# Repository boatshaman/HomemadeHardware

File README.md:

# Homemade Hardware
### Projects from homemade hardware ITP course with Andrew Sigler 
##### Joseph Hensersky | JH5363

* [ATtiny85 Programming Rig in class exercise](https://github.com/boatshaman/HomemadeHardware/tree/master/ATtiny85_Jig)
* [ATtiny85 First Interaction](https://github.com/boatshaman/HomemadeHardware/tree/master/firstInteraction_ATtiny85)
* [Lipo Battery Charger Circuit Board in class exercise](https://github.com/boatshaman/HomemadeHardware/tree/master/lipo_batt_charger)
* [Eagle First Homework](https://github.com/boatshaman/HomemadeHardware/tree/master/EagleFirstHW)
* [Marquee Board - Letter 'O'](https://github.com/boatshaman/HomemadeHardware/tree/master/Marquee)
* [Final Project BOM](https://github.com/boatshaman/HomemadeHardware/blob/master/FinalProject_BOM)
* [Final Project](https://github.com/boatshaman/HomemadeHardware/tree/master/Final%20Board)

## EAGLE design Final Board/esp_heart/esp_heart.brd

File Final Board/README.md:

# Final Board - Capacitive Touch Heart

Okay so my final board ended up being a heart shaped board that has LEDs in the front in the shape of a heart along with a capacitive touch pad in the front. The LEDs are turned on when the capactive touch pad is pressed. I used a SMD ATtiny85 as the microcontroller and had wires soldered to the programming pins originally and just desoldered them after it had been programmed correctly. Here are pictures of the board along with the board design: 

Board and Schematic files can be found [here](https://github.com/boatshaman/HomemadeHardware/tree/master/Final%20Board/finschem) and the parts list has been updated in my [Final Project BOM](https://github.com/boatshaman/HomemadeHardware/tree/master/FinalProject_BOM). 

I think the coolest part about this board is that all the copper pours on the front are actually connected to the microcontroller. The outermost heart is the LED ground connected to the transistor, middle heart is vcc, innermost heart is the capacitive touch pad. Figuring out how to do the DXF files, polygon stuff, and connecting them to specific nets was a bit of a struggle but afterwards I got really quite good at using these features in EAGLE.

[Here](https://www.youtube.com/watch?v=mon0F_LehNs) is a video of the interaction 

I wanted to connect this board to a project I was creating for another class that would have it connected to the Adafruit IO MQTT broker. Originally I was planning on connecting some of the wires from the board to an ESP8266 Feather Huzzah I had but then realized that I could just put the ESP8266 on the heart itself! The generic ESP8266 is small enough and then I wouldn't be restricted to having the board connected to the microcontroller through wires. I redesigned the board with the ESP8266 as the controller. Here is the picture of the new board design:

There are two major changes in this. First is the ESP8266 of course. The ESP8266 is interesting because there are a couple pins that need to be correctly wired up for programming. DIO0 and DIO15 need to be pulled to ground and DIO2 to VCC. DIO0 usually needs to not be connected to ground though so I had add a button which I would press during programming. Another thing I needed for programming but didn't realize until after I had the board printed was I needed a connection from reset to the FTDI USB to serial programmer. It was really nerve wracking when I first tried to program the board after assembling it all and the code just wouldn't upload. I got around this but physically holding a wire to this pin during programming. 

I also forgot to connect one of the nets :'( 
I got around this buy soldering a wire to complete the connection. 

The final change that was neccessary was adding a regulator because the ESP8266 module excepts a maximum input voltage of 3.6 volts and even the lipo batteries give off a higher voltage when fully charged. As I wasn't able to order parts for this I just looked around the hard lab to find a regulator and settled on the UA78M33CDCYR 3.3v regulator. This was a mistake. While this regulator does give off 3.3v, it needs above a 5 volt input voltage which my lipo batteries wouldn't be able to provide. I realized this when I connected my lipo battery to the completed board and I measured the voltage coming out of the regulator to be about .3 volts. I was able to get around this by attaching a 9v battery to the board. I made a 9v battery connector by ripping apart an old 9v battery and soldering to the connectors of it. 

After that I just uploaded code and removed the programming wires and it was good to go! I needed rubber bands around the heart to secure the battery though.

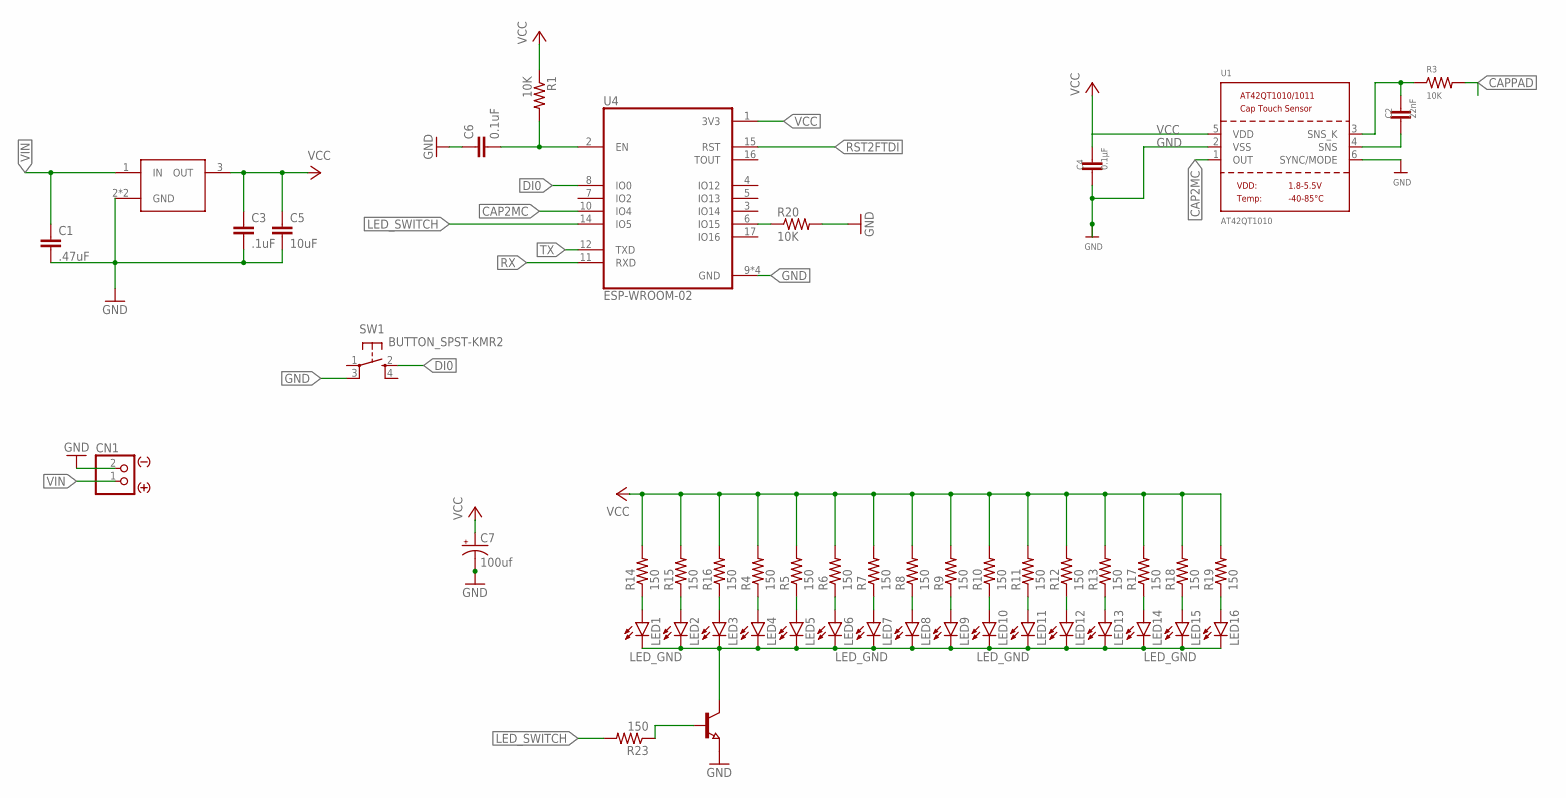
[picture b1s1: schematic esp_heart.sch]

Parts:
C1: .47uF; 0805
C2: 22nF; 0805
C3: .1uF; 0805
C4: 0.1µF; 0805
C5: 10uF; 0805
C6: 0.1uF; 0805
C7: 100uf; PANASONIC_D
CN1: JST_2PIN_BATTERY-SMT-HORIZ; JST-PH-2-SMT-RA
LED1, LED2, LED3, LED4, LED5, LED6, LED7, LED8, LED9, LED10, LED11, LED12, LED13, LED14, LED15, LED16: LED0603; LED-0603
Q5: TRANSISTOR-NPN-SOT23; SOT23
R1, R3, R20: 10K; 0805
R4, R5, R6, R7, R8, R9, R10, R11, R12, R13, R14, R15, R16, R17, R18, R19: 150; 0603-RES
R23: 150; 0805
SW1: BUTTON_SPST-KMR2; KMR2
U1: AT42QT1010; SOT23-6
U4: ESP-WROOM-02; MODULE_ESP-WROOM-02
U$1: REGULATOR3.3V-0.5A-UA78M33CDCYR; SOT223

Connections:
CAP2MC: U1.1 (OUT), U4.10 (IO4)
CAPPAD: R3.2
DI0: SW1.2 (S), U4.8 (IO0)
GND: C1.2, C3.2, C4.2, C5.2, C6.1, C7.-, CN1.2 (1), Q5.2 (E), R20.2, SW1.3 (P1), U1.2 (VSS), U1.6 (SYNC/MODE), U4.9 (GND), U4.13 (GND), U4.18 (GND), U4.19 (GND), U$1.2 (GND), U$1.4 (GND)
LED_GND: LED1.C, LED2.C, LED3.C, LED4.C, LED5.C, LED6.C, LED7.C, LED8.C, LED9.C, LED10.C, LED11.C, LED12.C, LED13.C, LED14.C, LED15.C, LED16.C, Q5.3 (C)
LED_SWITCH: R23.2, U4.14 (IO5)
unnamed: LED4.A, R4.1
unnamed: C6.2, R1.2, U4.2 (EN)
unnamed: LED15.A, R18.1
unnamed: LED1.A, R14.1
unnamed: LED2.A, R15.1
unnamed: LED5.A, R5.1
unnamed: LED6.A, R6.1
unnamed: LED7.A, R7.1
unnamed: LED8.A, R8.1
unnamed: LED9.A, R9.1
unnamed: LED10.A, R10.1
unnamed: LED11.A, R11.1
unnamed: LED12.A, R12.1
unnamed: LED13.A, R13.1
unnamed: LED3.A, R16.1
unnamed: R20.1, U4.6 (IO15)
unnamed: LED16.A, R19.1
unnamed: LED14.A, R17.1
unnamed: Q5.1 (B), R23.1
unnamed: C2.2, U1.4 (SNS)
unnamed: C2.1, R3.1, U1.3 (SNS_K)
RST2FTDI: U4.15 (RST)
RX: U4.11 (RXD)
TX: U4.12 (TXD)
VCC: C3.1, C4.1, C5.1, C7.+, R1.1, R4.2, R5.2, R6.2, R7.2, R8.2, R9.2, R10.2, R11.2, R12.2, R13.2, R14.2, R15.2, R16.2, R17.2, R18.2, R19.2, U1.5 (VDD), U4.1 (3V3), U$1.3 (OUT)
VIN: C1.1, CN1.1 (2), U$1.1 (IN)

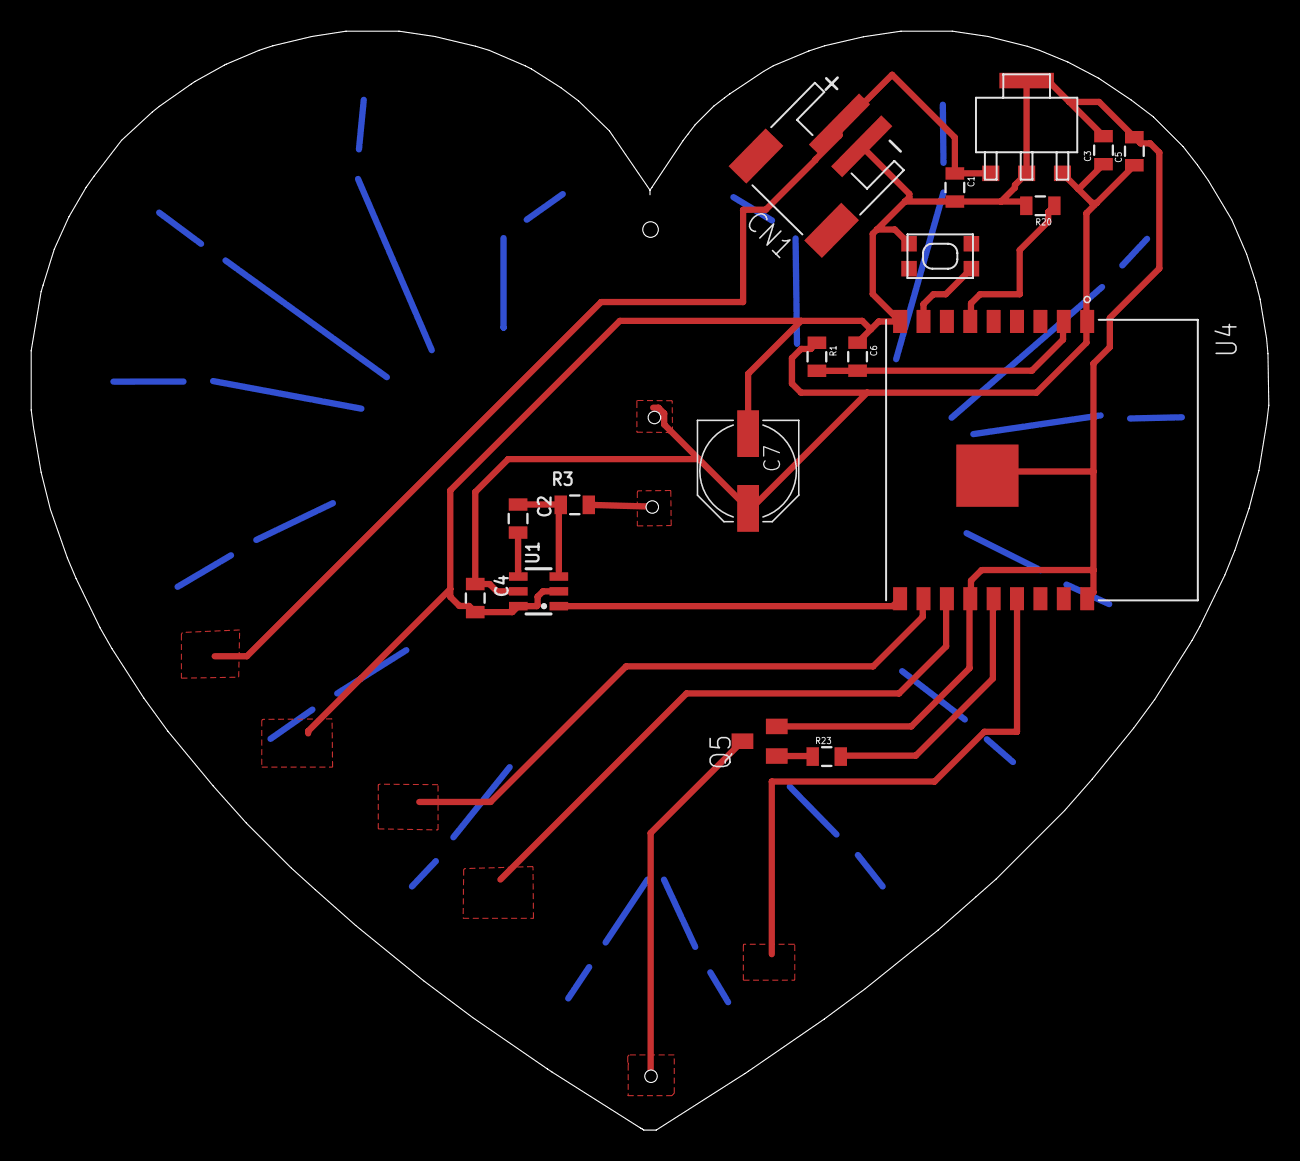
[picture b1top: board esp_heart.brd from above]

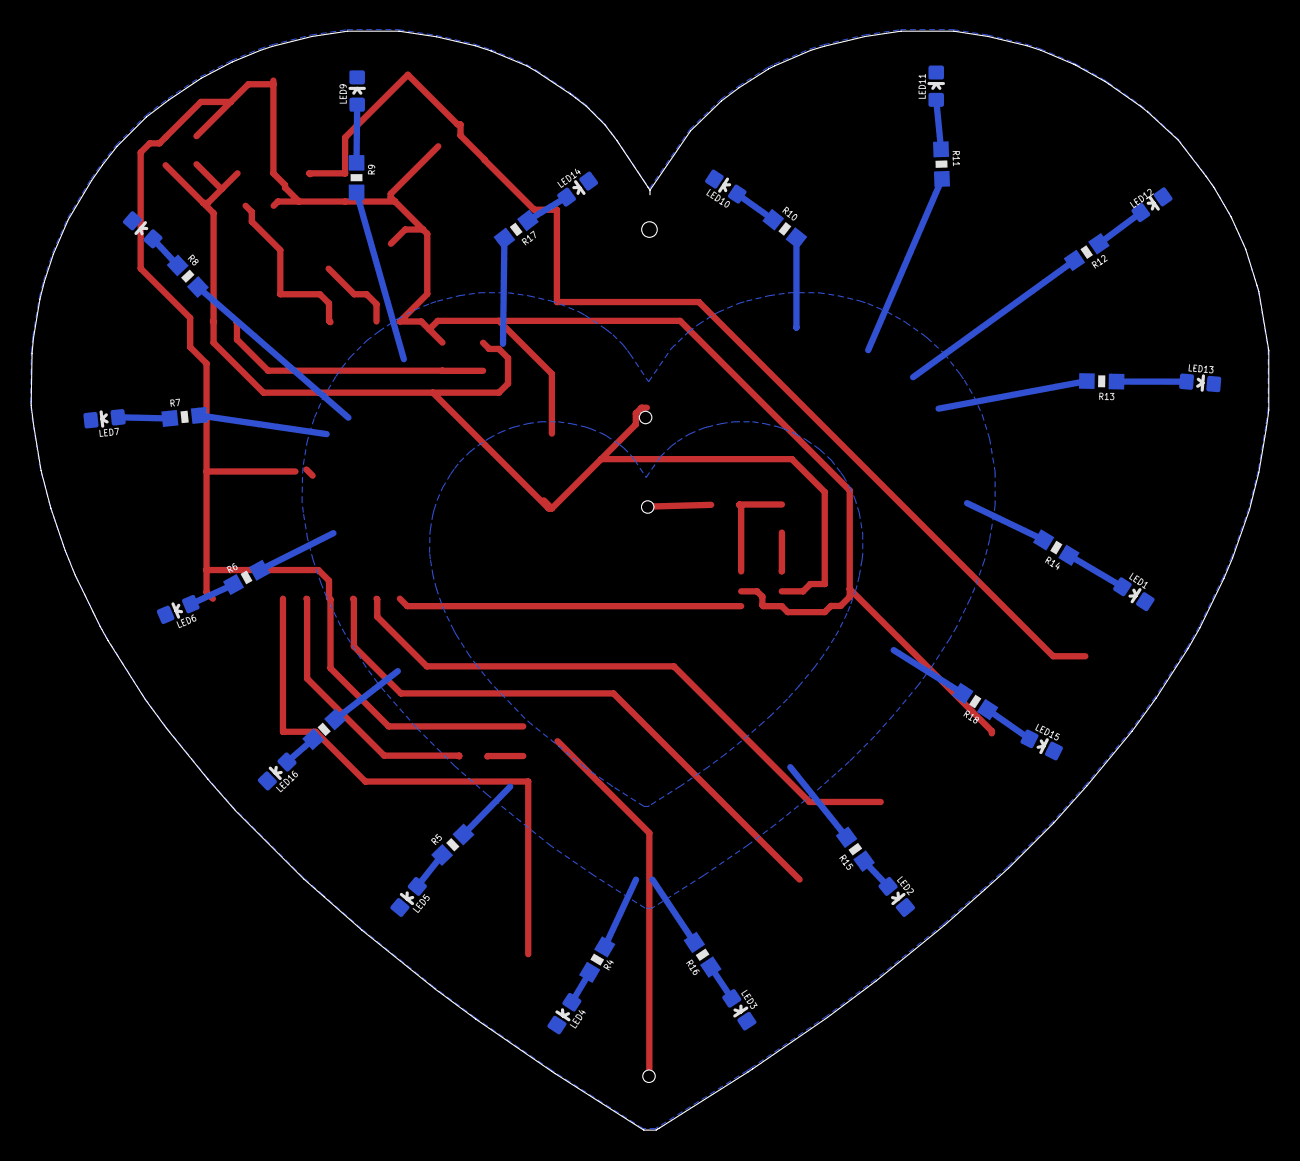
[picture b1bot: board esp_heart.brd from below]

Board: 2 copper layers, 79.4 x 70.5 mm, 49 parts (32 on the bottom side), 28 nets.

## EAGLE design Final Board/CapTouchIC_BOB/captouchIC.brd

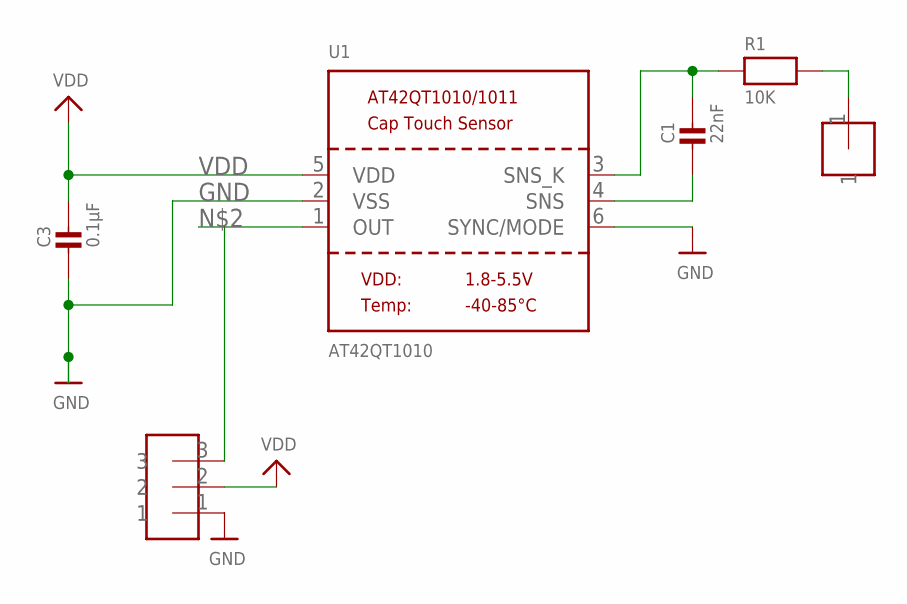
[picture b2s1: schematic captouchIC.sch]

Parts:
C1: 22nF; _0805
C3: 0.1µF; _0805
R1: 10K; _0805
U1: AT42QT1010; SOT23-6
U$1: HEADER-1-TESTPOINT; TESTPOINT-1
U$6: HEADER-3

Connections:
CAPPAD: R1.2, U$1.1
GND: C3.2, U1.2 (VSS), U1.6 (SYNC/MODE), U$6.1
unnamed: U1.1 (OUT), U$6.3
unnamed: C1.2, U1.4 (SNS)
unnamed: C1.1, R1.1, U1.3 (SNS_K)
VDD: C3.1, U1.5 (VDD), U$6.2

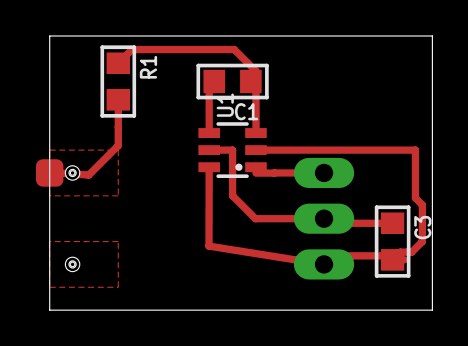
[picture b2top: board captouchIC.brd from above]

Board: 2 copper layers, 21.3 x 15.2 mm, 6 parts (0 on the bottom side), 6 nets.

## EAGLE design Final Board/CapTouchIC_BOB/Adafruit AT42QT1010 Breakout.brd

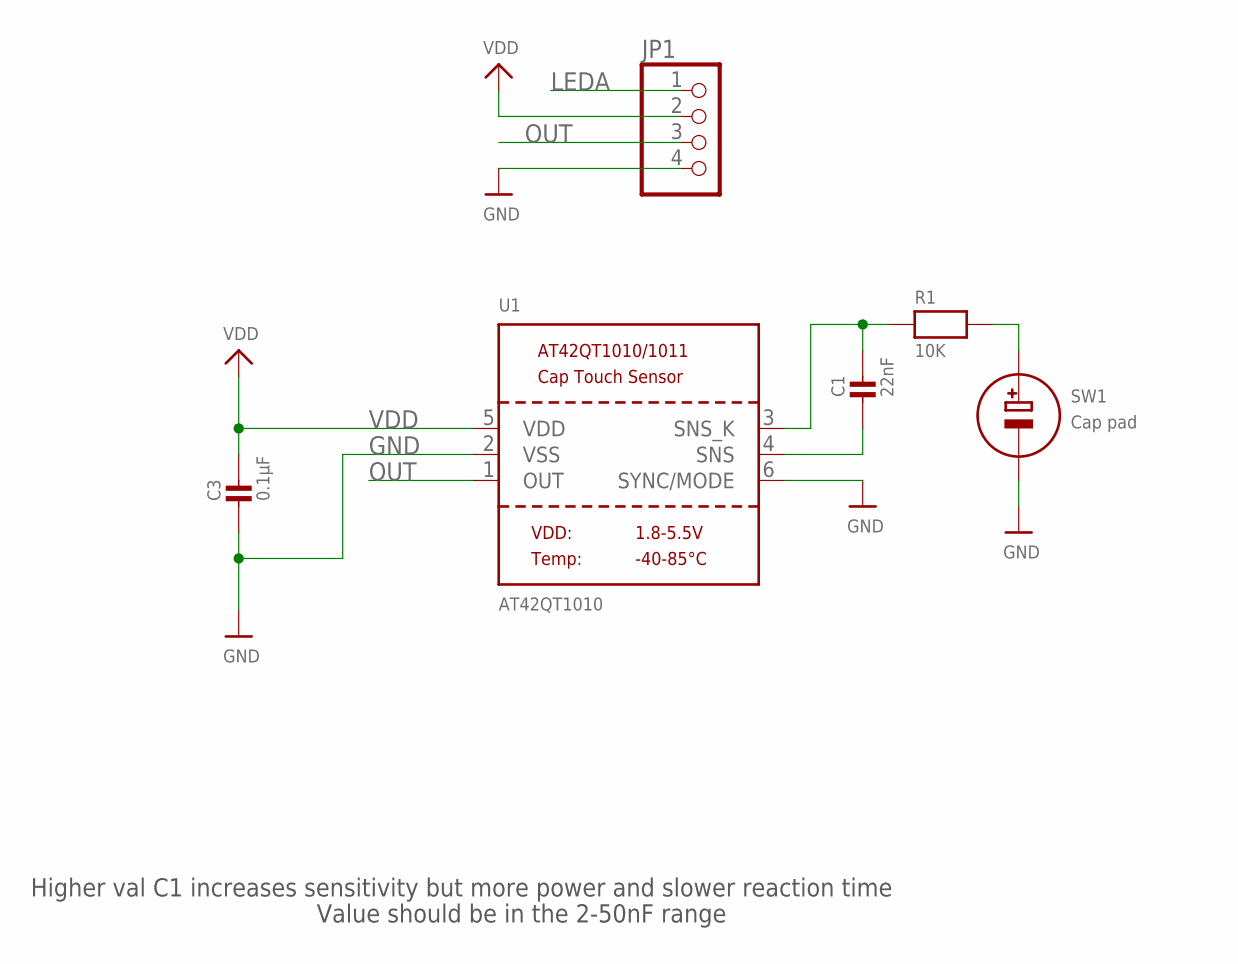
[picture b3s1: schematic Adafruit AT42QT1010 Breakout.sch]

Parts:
C1: 22nF; _0805
C3: 0.1µF; _0805
JP1: HEADER-1X476MIL; 1X04_ROUND_76
R1: 10K; _0805
SW1: Cap pad; CAPTOUCH_SIMPLE_12.5MM
U1: AT42QT1010; SOT23-6

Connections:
CAPPAD: R1.2, SW1.E (+)
GND: C3.2, JP1.4, SW1.G (-), U1.2 (VSS), U1.6 (SYNC/MODE)
LEDA: JP1.1
unnamed: C1.2, U1.4 (SNS)
unnamed: C1.1, R1.1, U1.3 (SNS_K)
OUT: JP1.3, U1.1 (OUT)
VDD: C3.1, JP1.2, U1.5 (VDD)

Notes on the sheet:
Higher val C1 increases sensitivity but more power and slower reaction time
Value should be in the 2-50nF range

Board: 2 copper layers, 6 parts (0 on the bottom side), 6 nets, no tracks yet.

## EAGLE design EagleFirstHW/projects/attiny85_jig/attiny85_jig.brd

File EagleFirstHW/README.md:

# Eagle Routing 

This homework is our first experience using the EAGLE software for the creation of PCB routing designs. 

We start with three different schematics and from that create .brd files which can be given to PCB mills in order to etch the routes onto a PCB board. While we haven't quite learned how to do that yet, this is the preliminary step and I am sure we will learn how to do this soon. 

#### ATTiny85 Programming Jig 

The first schematic we got was of the ATTiny85 Programming Jig just as we had created for our first week in-class exercise.

Here is the schematic file:

And here is my implementation of the routes for this schemeatic:

#### ATTiny85 LED 

The second schematic we got was of an ATTiny85 and LED setup. It seems this is just a very simple setup for controlling an LED with the ATTiny85

Here is the schematic file:

And here is my implementation of the routes for this schemeatic:

#### ATTiny85 Transistor 

The last schematic we got was of an ATTiny85 connected to a potentiometer and transistor. It seems to be a way for activating a larger power supply via the transistor to another electronic component. I am a little confused why a potentiometer is being used considering that is an analog switch and a transitor can only be off or on, but the professor said we will end up building this circuit board so I am sure we will find out. This one was defenitely the most difficult to figure out and I ended up needing to add a Via in order to finish the last connection. It is only one Via so it shouldn't be too difficult during the fabrication process and it gives me a chance to see what it takes to create a Via on a PCB board. 

Here is the schematic file:

And here is my implementation of the routes for this schemeatic:

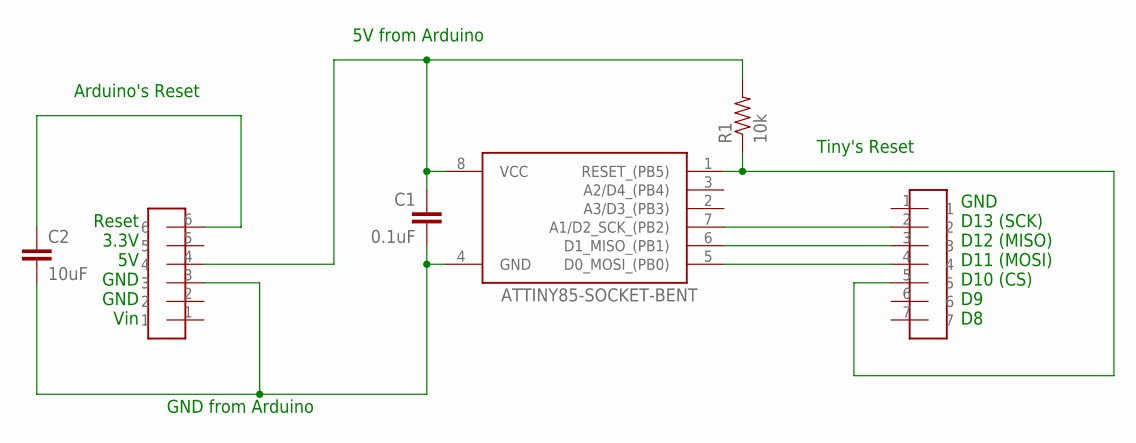
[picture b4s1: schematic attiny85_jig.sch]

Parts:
C1: 0.1uF; 0805
C2: 10uF; 0805
R1: 10k; 0805
U$1: ATTINY85-SOCKET-BENT; SOCKET-8PIN-BENT
U$2: HEADER-6
U$3: HEADER-7

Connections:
5V: C1.1, R1.2, U$1.8 (VCC), U$2.4
ARDUINO_RESET: C2.1, U$2.6
GND: C1.2, C2.2, U$1.4 (GND), U$2.3
MISO: U$1.6 (D1_MISO_(PB1)), U$3.3
MOSI: U$1.5 (D0_MOSI_(PB0)), U$3.4
SCK: U$1.7 (A1/D2_SCK_(PB2)), U$3.2
TINY_RESET: R1.1, U$1.1 (RESET_(PB5)), U$3.5

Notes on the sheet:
Arduino's Reset
GND D13 (SCK) D12 (MISO) D11 (MOSI) D10 (CS) D9 D8
Reset 3.3V 5V GND GND Vin
5V from Arduino
GND from Arduino
Tiny's Reset

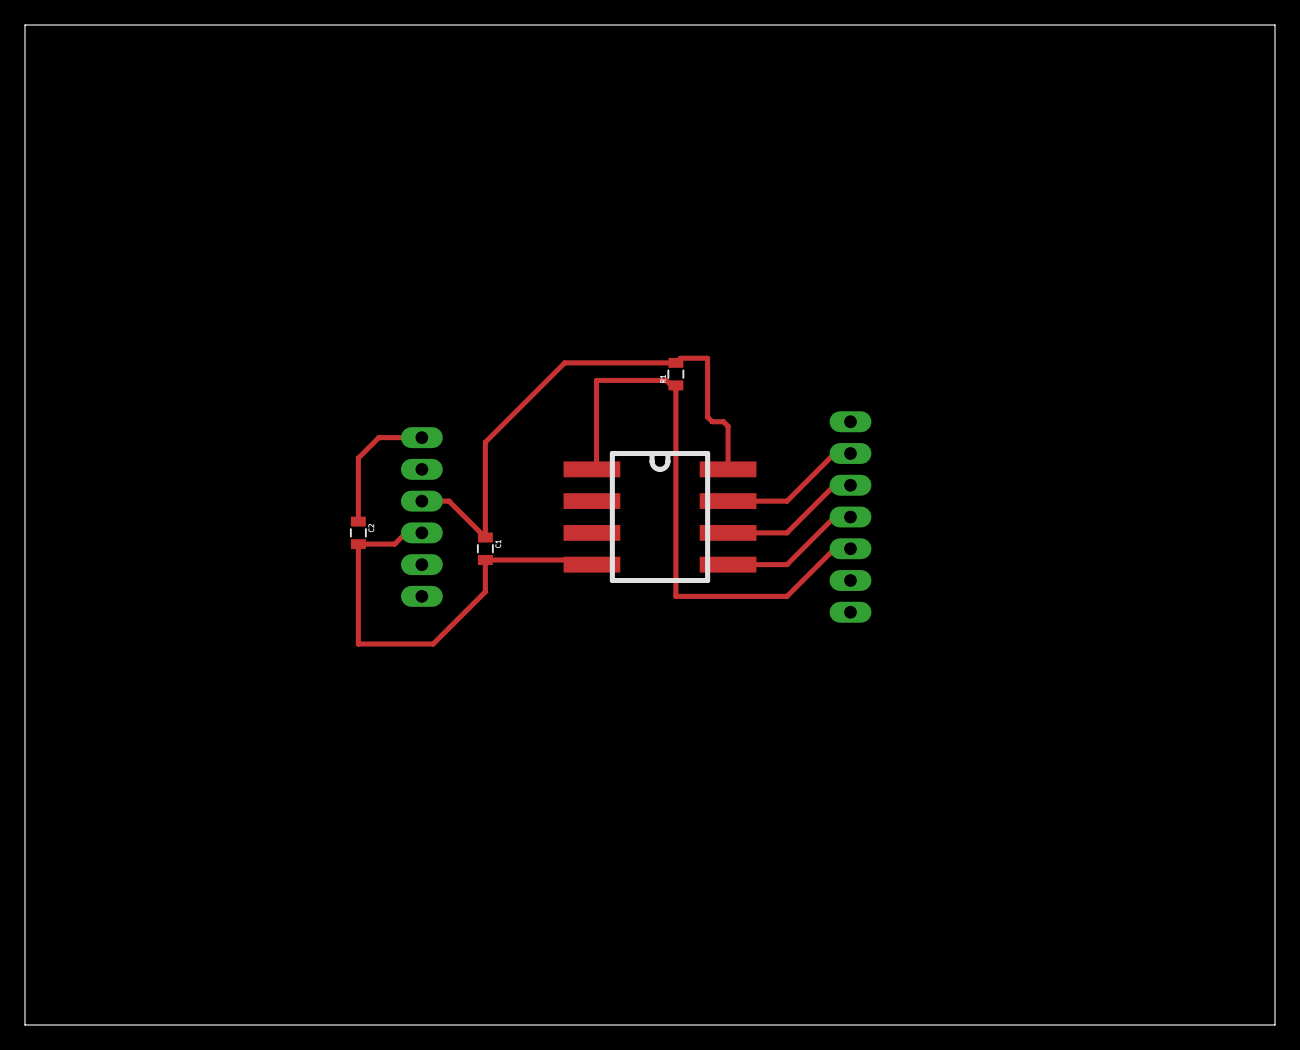
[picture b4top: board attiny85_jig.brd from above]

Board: 2 copper layers, 100.0 x 80.0 mm, 6 parts (0 on the bottom side), 7 nets.

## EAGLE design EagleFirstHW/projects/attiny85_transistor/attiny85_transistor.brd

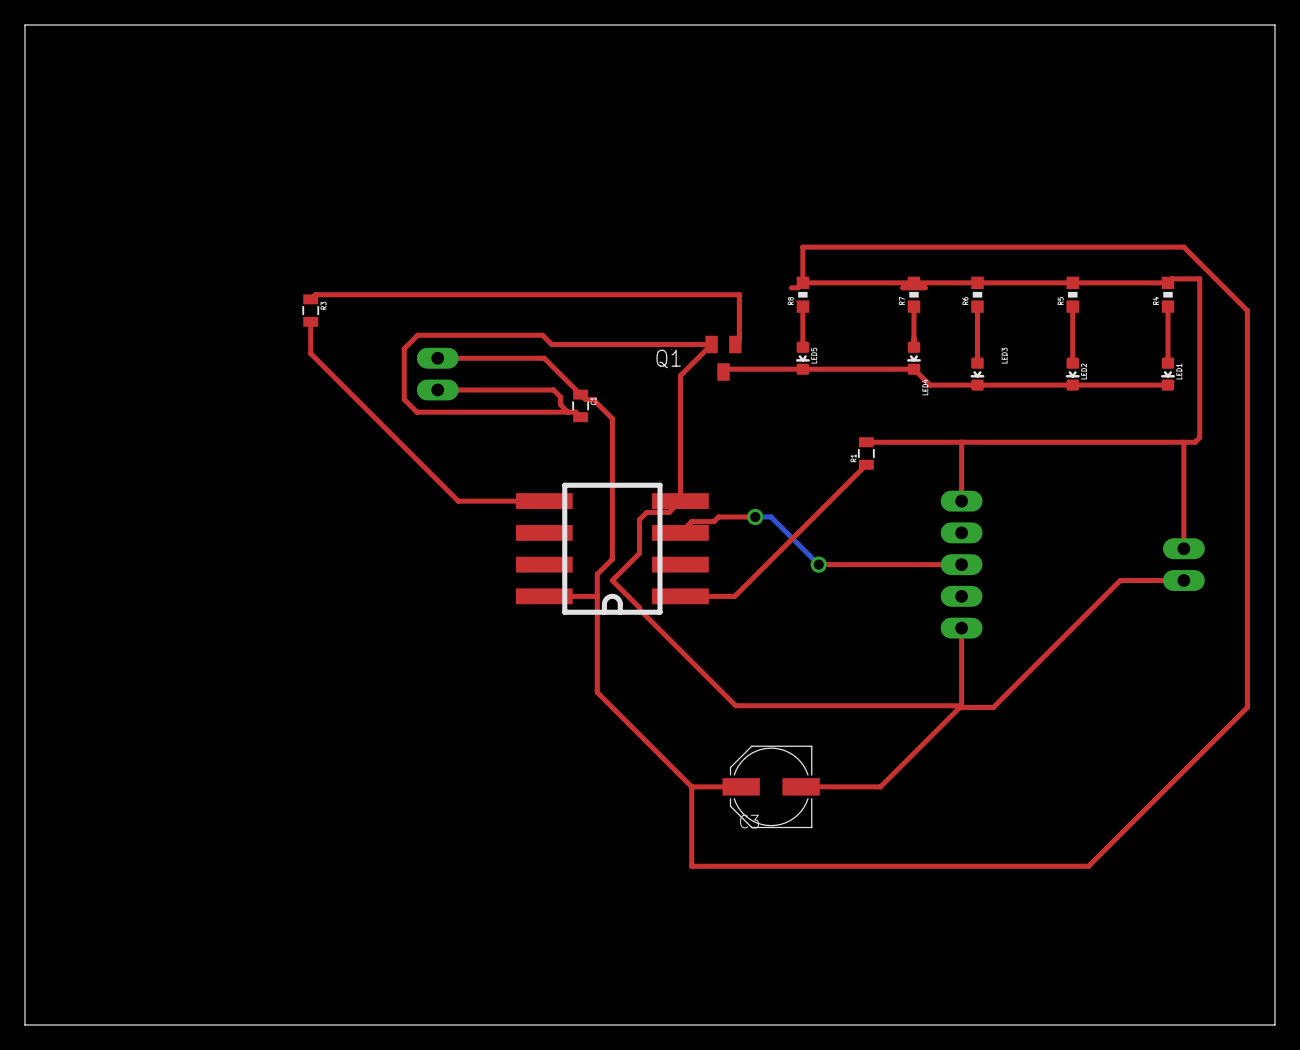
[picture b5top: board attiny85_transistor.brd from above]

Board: 2 copper layers, 100.0 x 80.0 mm, 19 parts (0 on the bottom side), 12 nets.

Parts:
C1: 0.1uF; 0805
C3: 100uF; PANASONIC_D
LED1, LED2, LED3, LED4, LED5: LED-0603
POTENTIOMETER: HEADER-5
Q1: BSH103; SOT23
R1: 10k; 0805
R3: 150; 0805
R4, R5, R6, R7, R8: 0603-RES
U$1: ATTINY85-SOCKET-BENT; SOCKET-8PIN-BENT
U$2, U$3: HEADER-2

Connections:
5V: C1.1, C3.+, POTENTIOMETER.1, R1.2, R4.2, R5.2, R6.2, R7.2, R8.2, U$1.8, U$2.2, U$3.1
GND: C1.2, C3.-, POTENTIOMETER.5, Q1.2, U$1.4, U$2.1, U$3.2
unnamed: LED1.A, R4.1
unnamed: R3.2, U$1.5
unnamed: LED1.C, LED2.C, LED3.C, LED4.C, LED5.C, Q1.3
unnamed: Q1.1, R3.1
unnamed: LED2.A, R5.1
unnamed: LED3.A, R6.1
unnamed: LED4.A, R7.1
unnamed: LED5.A, R8.1
unnamed: R1.1, U$1.1
SENSOR: POTENTIOMETER.3, U$1.3

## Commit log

2019-03-26 adding first exercise
2019-03-27 adding pics
2019-03-29 add new project
2019-03-29 adding vid
2019-03-29 added c code
2019-03-29 changing gif
2019-04-02 new dir for in-class exercise
2019-04-02 added readme to lipo charger
2019-04-02 editing
2019-04-02 edited pics
2019-04-04 adding Eagle First HW dir
2019-04-04 changing pic
2019-04-16 adding marquee
2019-04-16 organize marquee + add pics
2019-04-23 adding BOM dir
2019-05-08 add final project directory
2019-05-08 fix extra
2019-05-10 adding media for final
2019-05-10 readme for final board
2019-05-10 add esp heart schem and board file
2019-05-10 adding more pictures for final
2019-05-10 edit file names
2019-05-10 resize images
2019-05-10 debug size
2019-05-10 another resize
2019-05-11 new board pictures

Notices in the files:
parts and their libraries:
microbuilder: This work is placed in the public domain, and may be freely used for commercial and non-commercial work with the following conditions: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
